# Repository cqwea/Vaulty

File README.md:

# Vaulty

## About
A small money tracker for money savers which fetches the current rates and you type in your bought goods and title keep track of it and show you a portfolio that'll motivate you
## Features
1- İt can fetch currency rates online and update your savings to that
2-stores all the entries as history so you can see what you bought and what was the rates at that time being
3-Portfolio that you can see to get motivated of how much you've saved
4-Safe because no data leaves your device
## Assembly

## Case

## Schematics

## PCB

## Renders

## Aİ
NOPE

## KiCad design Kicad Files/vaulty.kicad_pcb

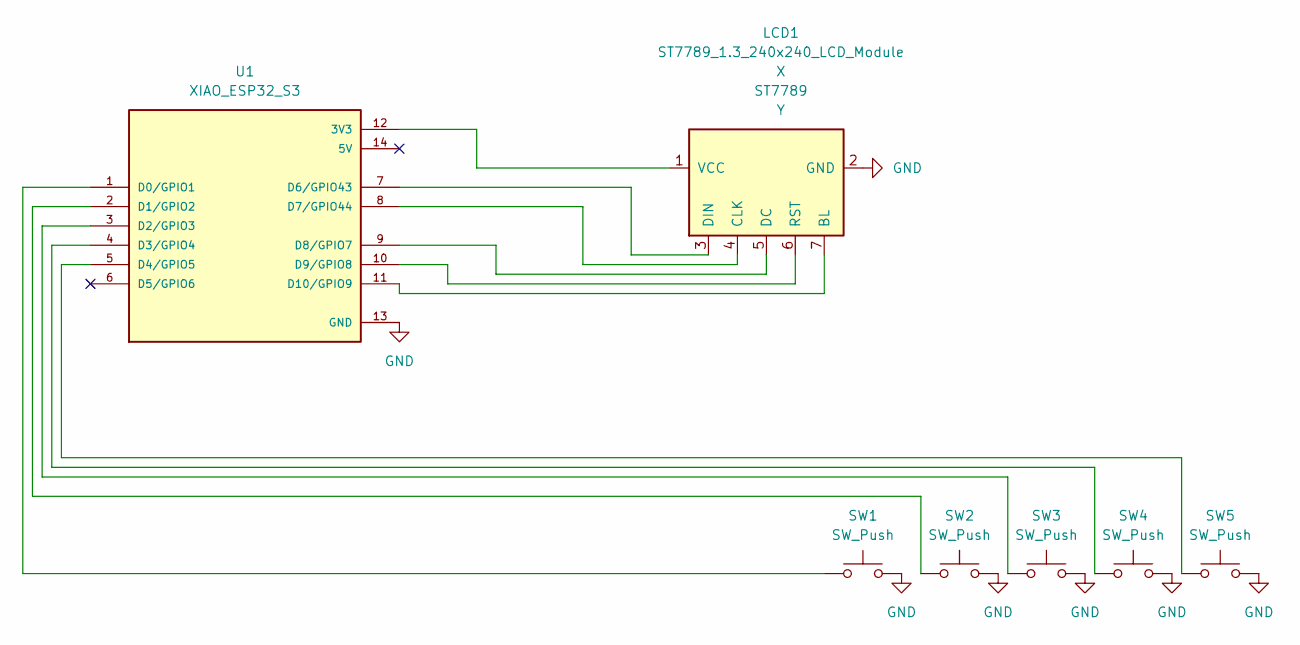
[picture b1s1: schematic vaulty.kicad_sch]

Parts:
LCD1: ST7789_1.3_240x240_LCD_Module
SW1, SW2, SW3, SW4, SW5: SW_Push; SW_Cherry_MX_1.00u_PCB
U1: XIAO_ESP32_S3; MODULE_XIAO_ESP32_S3; PARTREV April 22nd, 2026

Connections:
GND: LCD1.2 (GND), SW1.2, SW2.2, SW3.2, SW4.2, SW5.2, U1.13 (GND)
unnamed: LCD1.7 (BL), U1.11 (D10/GPIO9)
unnamed: LCD1.4 (CLK), U1.8 (D7/GPIO44)
unnamed: LCD1.5 (DC), U1.9 (D8/GPIO7)
unnamed: LCD1.3 (DIN), U1.7 (D6/GPIO43)
unnamed: LCD1.6 (RST), U1.10 (D9/GPIO8)
unnamed: LCD1.1 (VCC), U1.12 (3V3)
unnamed: SW1.1, U1.1 (D0/GPIO1)
unnamed: SW2.1, U1.2 (D1/GPIO2)
unnamed: SW3.1, U1.3 (D2/GPIO3)
unnamed: SW4.1, U1.4 (D3/GPIO4)
unnamed: SW5.1, U1.5 (D4/GPIO5)

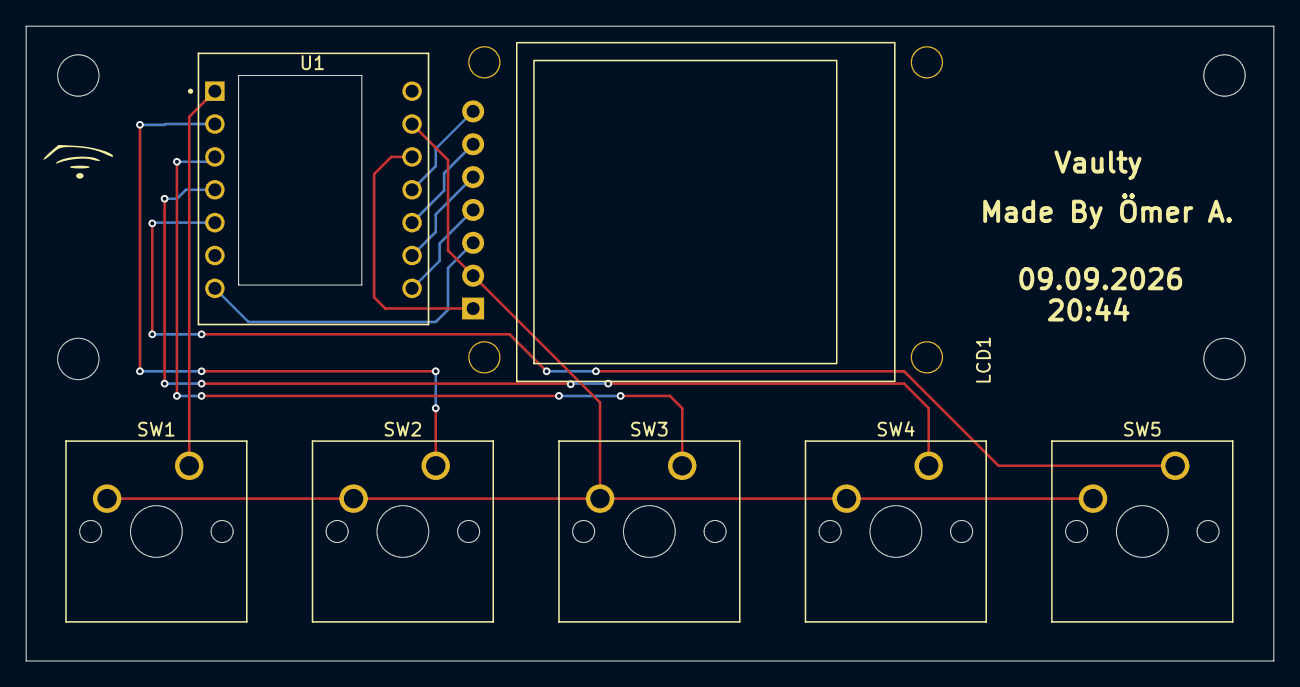
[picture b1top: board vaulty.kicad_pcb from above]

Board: 2 copper layers, 96.4 x 49.1 mm, 7 parts (0 on the bottom side), 12 nets.
